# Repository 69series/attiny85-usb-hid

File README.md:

# ATtiny85 USB HID Keyboard

A fully custom USB HID keyboard dongle built on ATtiny85 — bare metal C firmware,
custom PCB designed in KiCad 10, no Arduino, no HAL, no bootloader abstractions.
Plug it into any USB port and it enumerates as a real HID keyboard device.

---

# ATtiny85 USB HID Keyboard

A fully custom USB HID keyboard dongle...

## What it does

Plugs directly into a USB-A port and acts as an autonomous HID keyboard.
Planned automation payloads (see `firmware/` for examples):

- One-click temp folder cleaner (`Win+R → %temp% → Ctrl+A → Shift+Del`)
- Stored credential injector (password manager dongle)
- Custom keyboard macro sequences
- Any HID keystroke automation — limited only by firmware logic

---

## Hardware

| Part | Value | Package |
|------|-------|---------|
| U1 | ATtiny85-20SU | SOIC-8 |
| R1, R2 | 68Ω | 1206 |
| R3 | 1.5kΩ (pull-up) | 1206 |
| R4 | 1.5kΩ (LED) | 1206 |
| C1 | 100nF | 0805 |
| D1, D2 | 3.6V Zener | SOD-123 |
| D3 | LED | 0402 |
| J1 | USB-FX | Custom PCB-edge footprint |

**PCB:** 31.31 × 11.8 × 0.8mm — slides directly into USB-A female socket.
Custom USB-FX footprint — PCB edge pads act as USB-A plug contacts.
Designed in KiCad 10. Ground pour on F.Cu.

**Schematic:** `docs/schematic.png`
**PCB Layout:** `docs/pcb.png`
**3D Render:** `docs/3dpcb_front.png` / `docs/3dpcb_back.png`
**Gerbers + BOM:** `hardware/fabrication/`

---

### Schematic

### PCB Layout

### 3D Render

## Firmware

Pure bare-metal C. No Arduino core, no HAL, no bootloader.
Uses the V-USB library (obdev, v20121206) for software USB bit-banging on PB3/PB4.

**Toolchain:** avr-gcc (WinAVR), avrdude, VS Code

### Build and flash

```bash
cd firmware
make
make fuses
make flash
```

Or use the included automation script:

```bash
69s.bat -unlock -17A
```

### Fuse bits

```bash
avrdude -c usbasp -p attiny85 -U lfuse:w:0xE1:m -U hfuse:w:0xDD:m
```

- `lfuse 0xE1` — internal 16.5MHz PLL oscillator (required for V-USB timing)
- `hfuse 0xDD` — RESET enabled, SPI programming on

### Pin mapping

| ATtiny85 Pin | Function |
|--------------|----------|
| PB3 (pin 2) | USB D− |
| PB4 (pin 3) | USB D+ |
| PB2 (pin 7) | Status LED |
| PB0 (pin 5) | ICSP MOSI / TP2 |
| PB1 (pin 6) | ICSP MISO / TP3 |
| PB2 (pin 7) | ICSP SCK / TP4 |
| PB5 (pin 1) | RESET / TP5 |

---

## Project Structure

```
attiny85-usb-hid/
├── docs/                     # Schematic, PCB renders, design notes
│   ├── schematic.png
│   ├── pcb.png
│   ├── 3dpcb_front.png
│   ├── 3dpcb_back.png
│   └── design-notes.md
├── firmware/                 # Bare metal C firmware
│   ├── main.c                # Main application
│   ├── usbconfig.h           # V-USB hardware configuration
│   ├── Makefile
│   ├── 69s.bat               # One-shot build+flash automation
│   └── usbdrv/               # V-USB library (obdev v20121206)
├── hardware/
│   ├── fabrication/          # Gerbers, BOM, positions for JLCPCB
│   │   ├── t85-gerber.zip
│   │   ├── bom.csv
│   │   └── positions.csv
│   ├── hardware_prototype/   # Prototype build photos, all versions
│   │   ├── spider_config.jpeg        # Initial 6-wire ICSP test setup
│   │   ├── vers_1_front.jpeg         # Version 1 prototype
│   │   ├── vers_1_back.jpeg
│   │   ├── final_cleanup_version_front.jpg  # Final build (PB4 hot-wired)
│   │   └── final_cleanup_version_back.jpg
│   ├── t85-usb.kicad_sch
│   ├── t85-usb.kicad_pcb
│   └── t85-usb.pdf
└── README.md
```
---

## Key Design Decisions

**Why ATtiny85?** 8-pin SOIC, 8KB flash, runs at 16.5MHz via internal PLL —
no external crystal needed, freeing PB3/PB4 for USB D+/D−.

**Why bare metal C?** Full control over every cycle. No Arduino abstraction layer,
no bootloader overhead. USB enumeration, HID descriptors, OSCCAL calibration —
all implemented and understood at the register level.

**Why V-USB?** ATtiny85 has no hardware USB peripheral. V-USB bit-bangs USB
low-speed (1.5 Mbit/s) in software using hand-tuned AVR assembly timed to
the exact cycle. This is the same approach used by Digispark.

**USB signal conditioning:** ATtiny85 GPIO swings 0–5V but USB data lines
must not exceed 3.3V. D1/D2 (3.6V zeners) clamp the high state.
R1/R2 (68Ω) provide impedance matching for the transmission line.

**OSCCAL runtime calibration:** Internal RC oscillator has ±10% factory
tolerance. V-USB requires ±1% at 16.5MHz. `calibrateOscillator()` uses
`usbMeasureFrameLength()` on every power-up to tune OSCCAL to the exact
live USB SOF timing, ensuring reliable enumeration regardless of temperature
or chip-to-chip variance.

**VID/PID:** Uses V-USB's shared free VID/PID pool (0x16C0 / 0x27DB).
Appropriate for open-source/personal projects per obdev's usage terms.

**Double enumeration init:** Two disconnect/reconnect cycles on startup —
the first lets the host settle/timeout on an initial connection attempt,
the second is the real enumeration. This mirrors the bootloader-exit →
user-program-start transition pattern and significantly improves
host compatibility, particularly on modern xHCI controllers.

**Windows driver binding:** Chose PID 0x27DB (matching Digispark's HID
keyboard PID) to ensure Windows binds the device to `hidusb.sys` (the
native HID class driver) rather than `libusb0.sys`. This is critical —
a generic libusb driver does not poll the interrupt-IN endpoint at the OS
level, so keystrokes never reach the active application regardless of
how correctly the USB descriptors enumerate.

---

## Host Compatibility

Tested and working:

| Host | Result |
|------|--------|
| Windows 11 (ASUS TUF F15, xHCI) | ✅ Full enumeration, keystrokes delivered |
| Android (Redmi Note 10 Pro, OTG) | ✅ Working |
| Android (Redmi 6, OTG) | ⚠️ Enumeration succeeds, keystrokes inconsistent |

---

## Prototype Notes

Built and tested on perfboard before PCB fabrication.
`hardware/prototype/spider_config.jpeg` shows the initial 6-wire ICSP
test harness soldered directly to the chip legs before any perfboard work.
`final_cleanup_version_*` shows the final prototype — PB4 (USB D+) pin
was damaged during rework and required a fine wire hot-fix, which held
reliably through all testing.

---

### Prototype Photos

---
## Debugging Journey

This project involved deep debugging across hardware, firmware, toolchain,
and host-compatibility layers. Notable findings:

- **OSCCAL drift** caused intermittent enumeration — solved with runtime
  calibration using `usbMeasureFrameLength()`
- **Windows driver binding** (libusb0 vs hidusb) was the root cause of
  keystrokes never arriving despite correct USB enumeration — identified
  by comparing working Digispark sketch logs against our own via UsbTreeView
- **xHCI interrupt-IN scheduling** behaves differently from legacy UHCI/OHCI
  for low-speed software-USB devices — characterized and worked around via
  double enumeration cycle and correct PID selection

Full debugging notes in `docs/design-notes.md`.

---

## Future Work

- [ ] Example firmware payloads (temp cleaner, credential injector, macro runner)
- [ ] PCB fabrication and SMD assembly at JLCPCB
- [ ] ICSP test pad verification on real PCB
- [ ] v2.0 PCB with ICSP pads on back copper for in-circuit reprogramming

---

## Author

**Narendra Sagolsem** — Electronics Engineer
Portfolio: [s69series-3-0.vercel.app](https://s69series-3-0.vercel.app)
GitHub: [69series](https://github.com/69series)

---

## License

Firmware: MIT
V-USB library: GPL v2 — see `firmware/usbdrv/License.txt`
Hardware: CERN-OHL-S v2

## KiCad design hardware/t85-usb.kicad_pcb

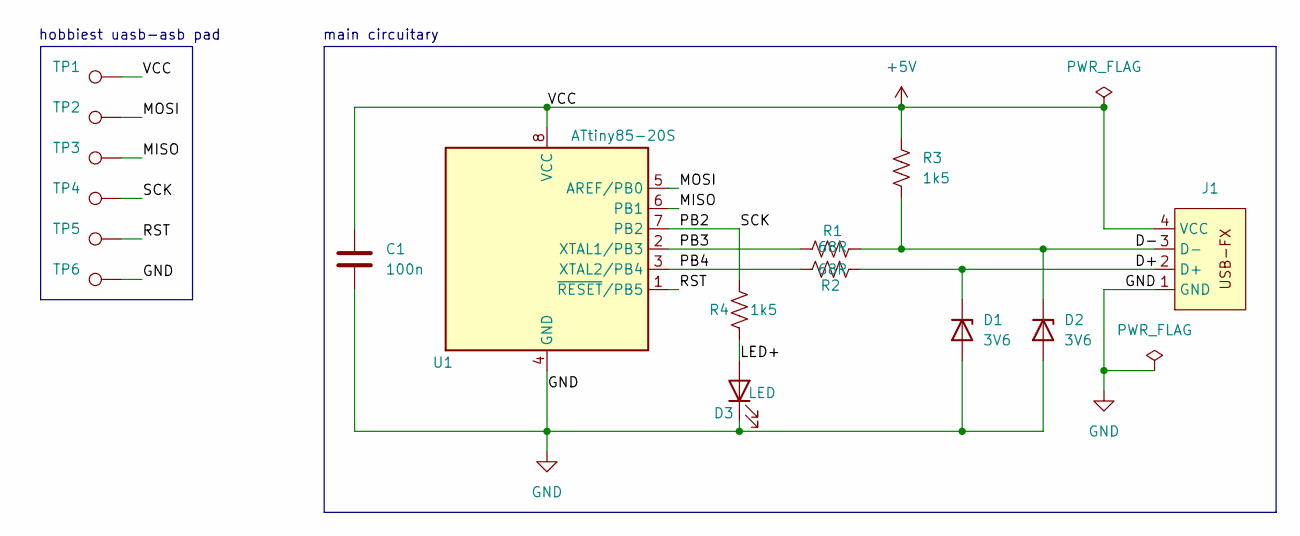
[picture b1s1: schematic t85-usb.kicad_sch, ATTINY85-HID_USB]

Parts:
C1: 100n; C_0805_2012Metric_Pad1.18x1.45mm_HandSolder
D1, D2: 3V6; D_SOD-123
D3: LED; LED_0805_2012Metric_Pad1.15x1.40mm_HandSolder
J1: USB-FX
R1, R2: 68R; R_1206_3216Metric_Pad1.30x1.75mm_HandSolder
R3, R4: 1k5; R_1206_3216Metric_Pad1.30x1.75mm_HandSolder
TP1, TP2, TP3, TP4, TP5, TP6: TestPoint; pad-0-8mm69s
U1: ATtiny85-20S; SOIC-8_5.3x5.3mm_P1.27mm

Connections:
+5V: C1.1, J1.4 (VCC), R3.1, TP1.1 (1_1), U1.8 (VCC)
/D+: D1.1 (K), J1.2 (D+), R2.2
/D-: D2.1 (K), J1.3 (D-), R1.2, R3.2
/LED+: D3.2 (A), R4.2
/MISO: TP3.1 (1_1), U1.6 (PB1)
/MOSI: TP2.1 (1_1), U1.5 (AREF/PB0)
/PB2: R4.1, TP4.1 (1_1), U1.7 (PB2)
/PB3: R1.1, U1.2 (XTAL1/PB3)
/PB4: R2.1, U1.3 (XTAL2/PB4)
/RST: TP5.1 (1_1), U1.1 (~RESET/PB5)
GND: C1.2, D1.2 (A), D2.2 (A), D3.1 (K), J1.1 (GND), TP6.1 (1_1), U1.4 (GND)

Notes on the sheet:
main circuitary
hobbiest uasb-asb pad

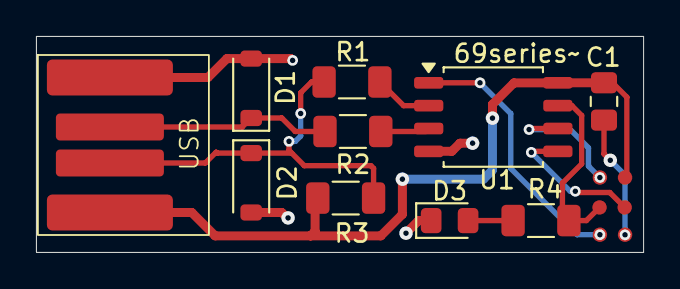
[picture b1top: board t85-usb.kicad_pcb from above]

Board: 2 copper layers, 33.7 x 12.0 mm, 16 parts (0 on the bottom side), 11 nets.

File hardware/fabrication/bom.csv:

Designator,Footprint,Quantity,Value,LCSC Part #
C1,0805,1,100n,
"D1, D2",D_SOD-123,2,3V6,
D3,0805,1,LED,
J1,USB-FX,1,~,
"R1, R2",1206,2,68R,
"R3, R4",1206,2,1k5,
"TP1, TP2, TP3, TP4, TP5, TP6",pad-0-8mm69s,6,TestPoint,
U1,SOIC-8_5.3x5.3mm_P1.27mm,1,ATtiny85-20S,

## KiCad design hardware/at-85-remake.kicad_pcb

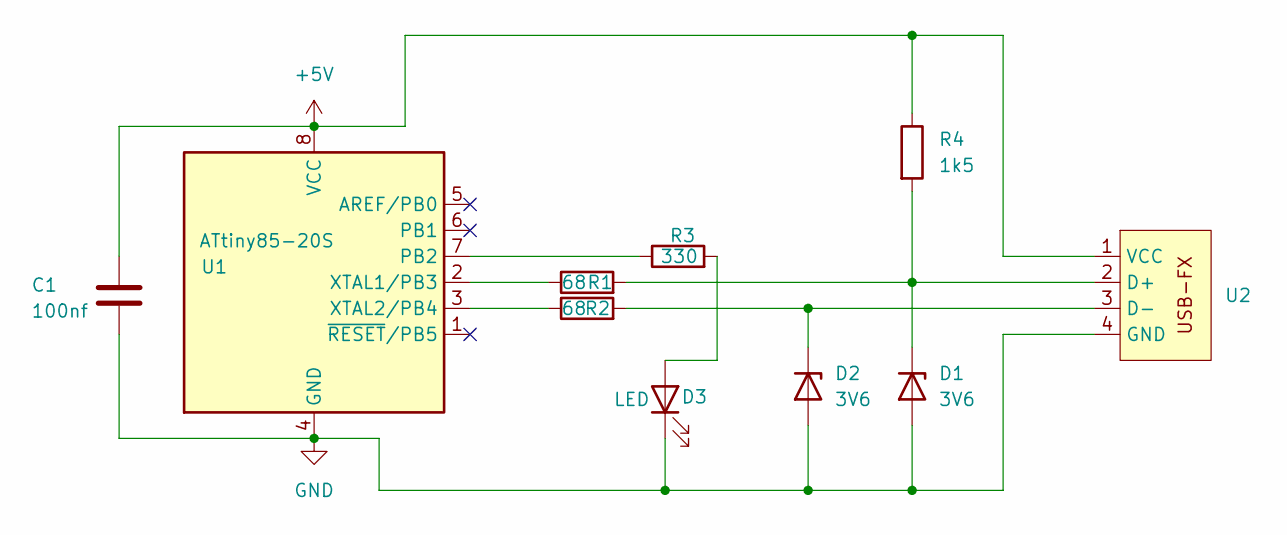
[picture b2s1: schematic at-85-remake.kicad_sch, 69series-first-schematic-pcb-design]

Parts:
C1: 100nf; C_1206_3216Metric_Pad1.33x1.80mm_HandSolder
D1, D2: 3V6; D_SOD-123
D3: LED; LED_1206_3216Metric
R1, R2: 68; R_0805_2012Metric
R3: 330; R_0805_2012Metric
R4: 1k5; R_0805_2012Metric
U1: ATtiny85-20S; SOIC-8_5.3x5.3mm_P1.27mm
U2: USB-FX

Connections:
+5V: C1.1, R4.1, U1.8 (VCC), U2.1 (VCC)
GND: C1.2, D1.2 (A), D2.2 (A), D3.1 (K), U1.4 (GND), U2.4 (GND); also elsewhere on the board
unnamed: D1.1 (K), R1.2, R4.2, U2.2 (D+)
unnamed: D2.1 (K), R2.2, U2.3 (D-)
unnamed 4: D3.2 (A), R3.2; also elsewhere on the board
unnamed: R3.1, U1.7 (PB2)
unnamed: R1.1, U1.2 (XTAL1/PB3)
unnamed: R2.1, U1.3 (XTAL2/PB4)

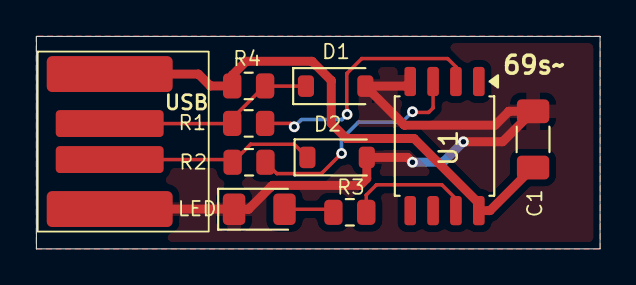
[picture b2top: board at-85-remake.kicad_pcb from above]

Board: 2 copper layers, 31.3 x 11.8 mm, 10 parts (0 on the bottom side), 8 nets.

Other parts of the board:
LED: LED; LED_1206_3216Metric

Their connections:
GND: LED.1 (K); also elsewhere on the board
unnamed 4: LED.2 (A); also elsewhere on the board

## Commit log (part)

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2026-06-02 feat: initial hardware design - ATtiny85 USB HID PCB
2026-06-02 chore: add firmware folder placeholder
2026-06-03 feat: bare metal V-USB HID keyboard firmware

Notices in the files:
README.md:
License: MIT
